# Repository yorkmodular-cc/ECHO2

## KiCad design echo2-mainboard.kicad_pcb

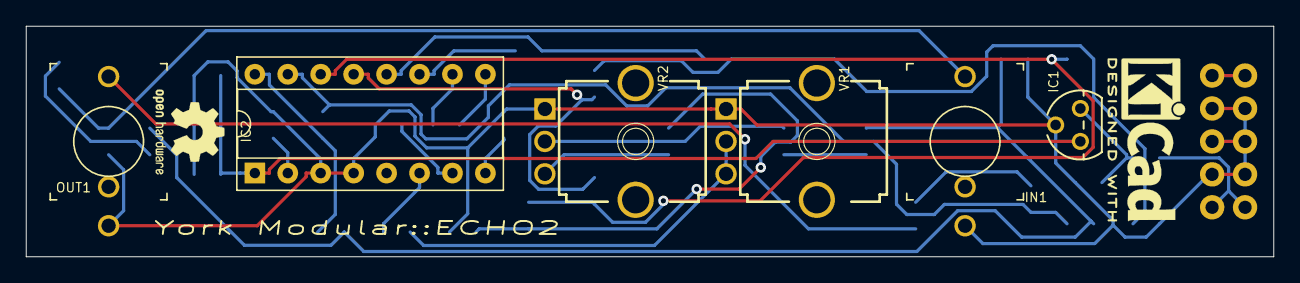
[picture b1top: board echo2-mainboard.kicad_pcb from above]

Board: 2 copper layers, 96.2 x 17.8 mm, 38 parts (0 on the bottom side), 28 nets.

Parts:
C1, C5, C6, C7: 0.1u; C_0805_2012Metric_Pad1.15x1.40mm_HandSolder
C2, C3, C15, C18: 10u; C_0805_2012Metric_Pad1.15x1.40mm_HandSolder
C4: 0.33u; C_0805_2012Metric_Pad1.15x1.40mm_HandSolder
C8, C9: 33n; C_0805_2012Metric_Pad1.15x1.40mm_HandSolder
C10, C11: 560p; C_0805_2012Metric_Pad1.15x1.40mm_HandSolder
C12: 3900p; C_0805_2012Metric_Pad1.15x1.40mm_HandSolder
C13: 10nF; C_0805_2012Metric_Pad1.15x1.40mm_HandSolder
C14, C17: 4.7u; C_0805_2012Metric_Pad1.15x1.40mm_HandSolder
C16: 3300p; C_0805_2012Metric_Pad1.15x1.40mm_HandSolder
D1: DIODE-SOD323-W; D_SOD-323_HandSoldering
IC1: 78Z; TO92
IC2: PT2399; DIP-16_W7.62mm_Socket
IN1: THONKICONNNEW; WQP-PJ301M-12_JACK
OUT1: THONKICONNNEW; WQP-PJ301M-12_JACK
POWER1: POWER_SIMPLE10; POWER_10
R1: FERRITE; R_0805_2012Metric_Pad1.15x1.40mm_HandSolder
R2: 1k; R_0805_2012Metric_Pad1.15x1.40mm_HandSolder
R3, R4, R6, R7, R8, R9, R11: 10k; R_0805_2012Metric_Pad1.15x1.40mm_HandSolder
R5: 5k6; R_0805_2012Metric_Pad1.15x1.40mm_HandSolder
R10: 100k; R_0805_2012Metric_Pad1.15x1.40mm_HandSolder
R12: 4k7; R_0805_2012Metric_Pad1.15x1.40mm_HandSolder
VR1: 20k; 9MM_SNAP-IN_POT
VR2: 50k; 9MM_SNAP-IN_POT

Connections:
+5V: C1.1, C2.1, C7.1, IC1.1, IC2.1
/ECHO: C18.2, OUT1.P$1_TIP
/IN: C17.2, IN1.P$1_TIP, R10.2
/OUT: C10.1, IC2.15, R4.1, R12.1
GND: C1.2, C2.2, C3.1, C4.2, C5.2, C6.2, C7.2, C12.2, C13.1, C16.1, IC1.2, IC2.3, IC2.4, IN1.P$3_SLEEVE, OUT1.P$3_SLEEVE, POWER1.3, POWER1.4, POWER1.5, POWER1.6, POWER1.7, POWER1.8, R10.1, VR1.1, VR2.1
unnamed: C3.2, IC2.2
unnamed: C4.1, IC1.3, R1.2
unnamed: C5.1, IC2.7
unnamed: C6.1, IC2.8
unnamed: C8.1, IC2.11
unnamed: C8.2, IC2.12, R8.1
unnamed: C9.1, IC2.9
unnamed: C9.2, IC2.10
unnamed: C10.2, IC2.16, R3.1
unnamed: C11.1, IC2.13, R7.1
unnamed: C11.2, IC2.14, R5.1, R6.1
unnamed: C12.1, C14.1, R3.2, R4.2, R9.1
unnamed: C13.2, C15.1, R5.2
unnamed: C14.2, R11.2
unnamed: C15.2, VR2.3
unnamed: C16.2, R6.2, R7.2, R8.2
unnamed: C17.1, R9.2
unnamed: C18.1, R12.2
unnamed: IC2.6, R2.2
unnamed: POWER1.1, POWER1.2
unnamed: POWER1.9, POWER1.10, R1.1
unnamed: R2.1, VR1.2, VR1.3
unnamed: R11.1, VR2.2

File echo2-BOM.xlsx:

Designator | Package | Quantity | Designation | Notes
IC2 | DIP-16_W7.62mm_Socket | 1 | PT2399
D1 | D_SOD-323_HandSoldering | 1 | DIODE-SOD323-W
R2 | R_0805_2012Metric_Pad1.15x1.40mm_HandSolder | 1 | 1k
R9,R8,R7,R6,R3,R4,R11 | R_0805_2012Metric_Pad1.15x1.40mm_HandSolder | 7 | 10k
R10 | R_0805_2012Metric_Pad1.15x1.40mm_HandSolder | 1 | 100k
R5 | R_0805_2012Metric_Pad1.15x1.40mm_HandSolder | 1 | 5k6
R12 | R_0805_2012Metric_Pad1.15x1.40mm_HandSolder | 1 | 4k7
R1 | R_0805_2012Metric_Pad1.15x1.40mm_HandSolder | 1 | FERRITE | Or 22R resistor
C5,C7,C6,C1 | C_0805_2012Metric_Pad1.15x1.40mm_HandSolder | 4 | 0.1u
C8,C9 | C_0805_2012Metric_Pad1.15x1.40mm_HandSolder | 2 | 33n
C10,C11 | C_0805_2012Metric_Pad1.15x1.40mm_HandSolder | 2 | 560p
C12 | C_0805_2012Metric_Pad1.15x1.40mm_HandSolder | 1 | 3900p
C4 | C_0805_2012Metric_Pad1.15x1.40mm_HandSolder | 1 | 0.33u
C13 | C_0805_2012Metric_Pad1.15x1.40mm_HandSolder | 1 | 10nF
C17,C14 | C_0805_2012Metric_Pad1.15x1.40mm_HandSolder | 2 | 4.7u
C15,C18,C3,C2 | C_0805_2012Metric_Pad1.15x1.40mm_HandSolder | 4 | 10u
C16 | C_0805_2012Metric_Pad1.15x1.40mm_HandSolder | 1 | 3300p
IC1 | TO92 | 1 | 78Z05 | 5V regulator
IN1,OUT1 | WQP-PJ301M-12_JACK | 2 | THONKICONNNEW
VR1 | 9MM_SNAP-IN_POT | 1 | 20k
VR2 | 9MM_SNAP-IN_POT | 1 | 50k
POWER1 | POWER_10 | 1 | POWER_SIMPLE10 | 2x5 power header

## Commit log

2022-05-15 Create LICENSE
